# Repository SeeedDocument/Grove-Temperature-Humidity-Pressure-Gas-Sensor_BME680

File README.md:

# Grove-Temperature-Humidity-Pressure-Gas-Sensor_BME680

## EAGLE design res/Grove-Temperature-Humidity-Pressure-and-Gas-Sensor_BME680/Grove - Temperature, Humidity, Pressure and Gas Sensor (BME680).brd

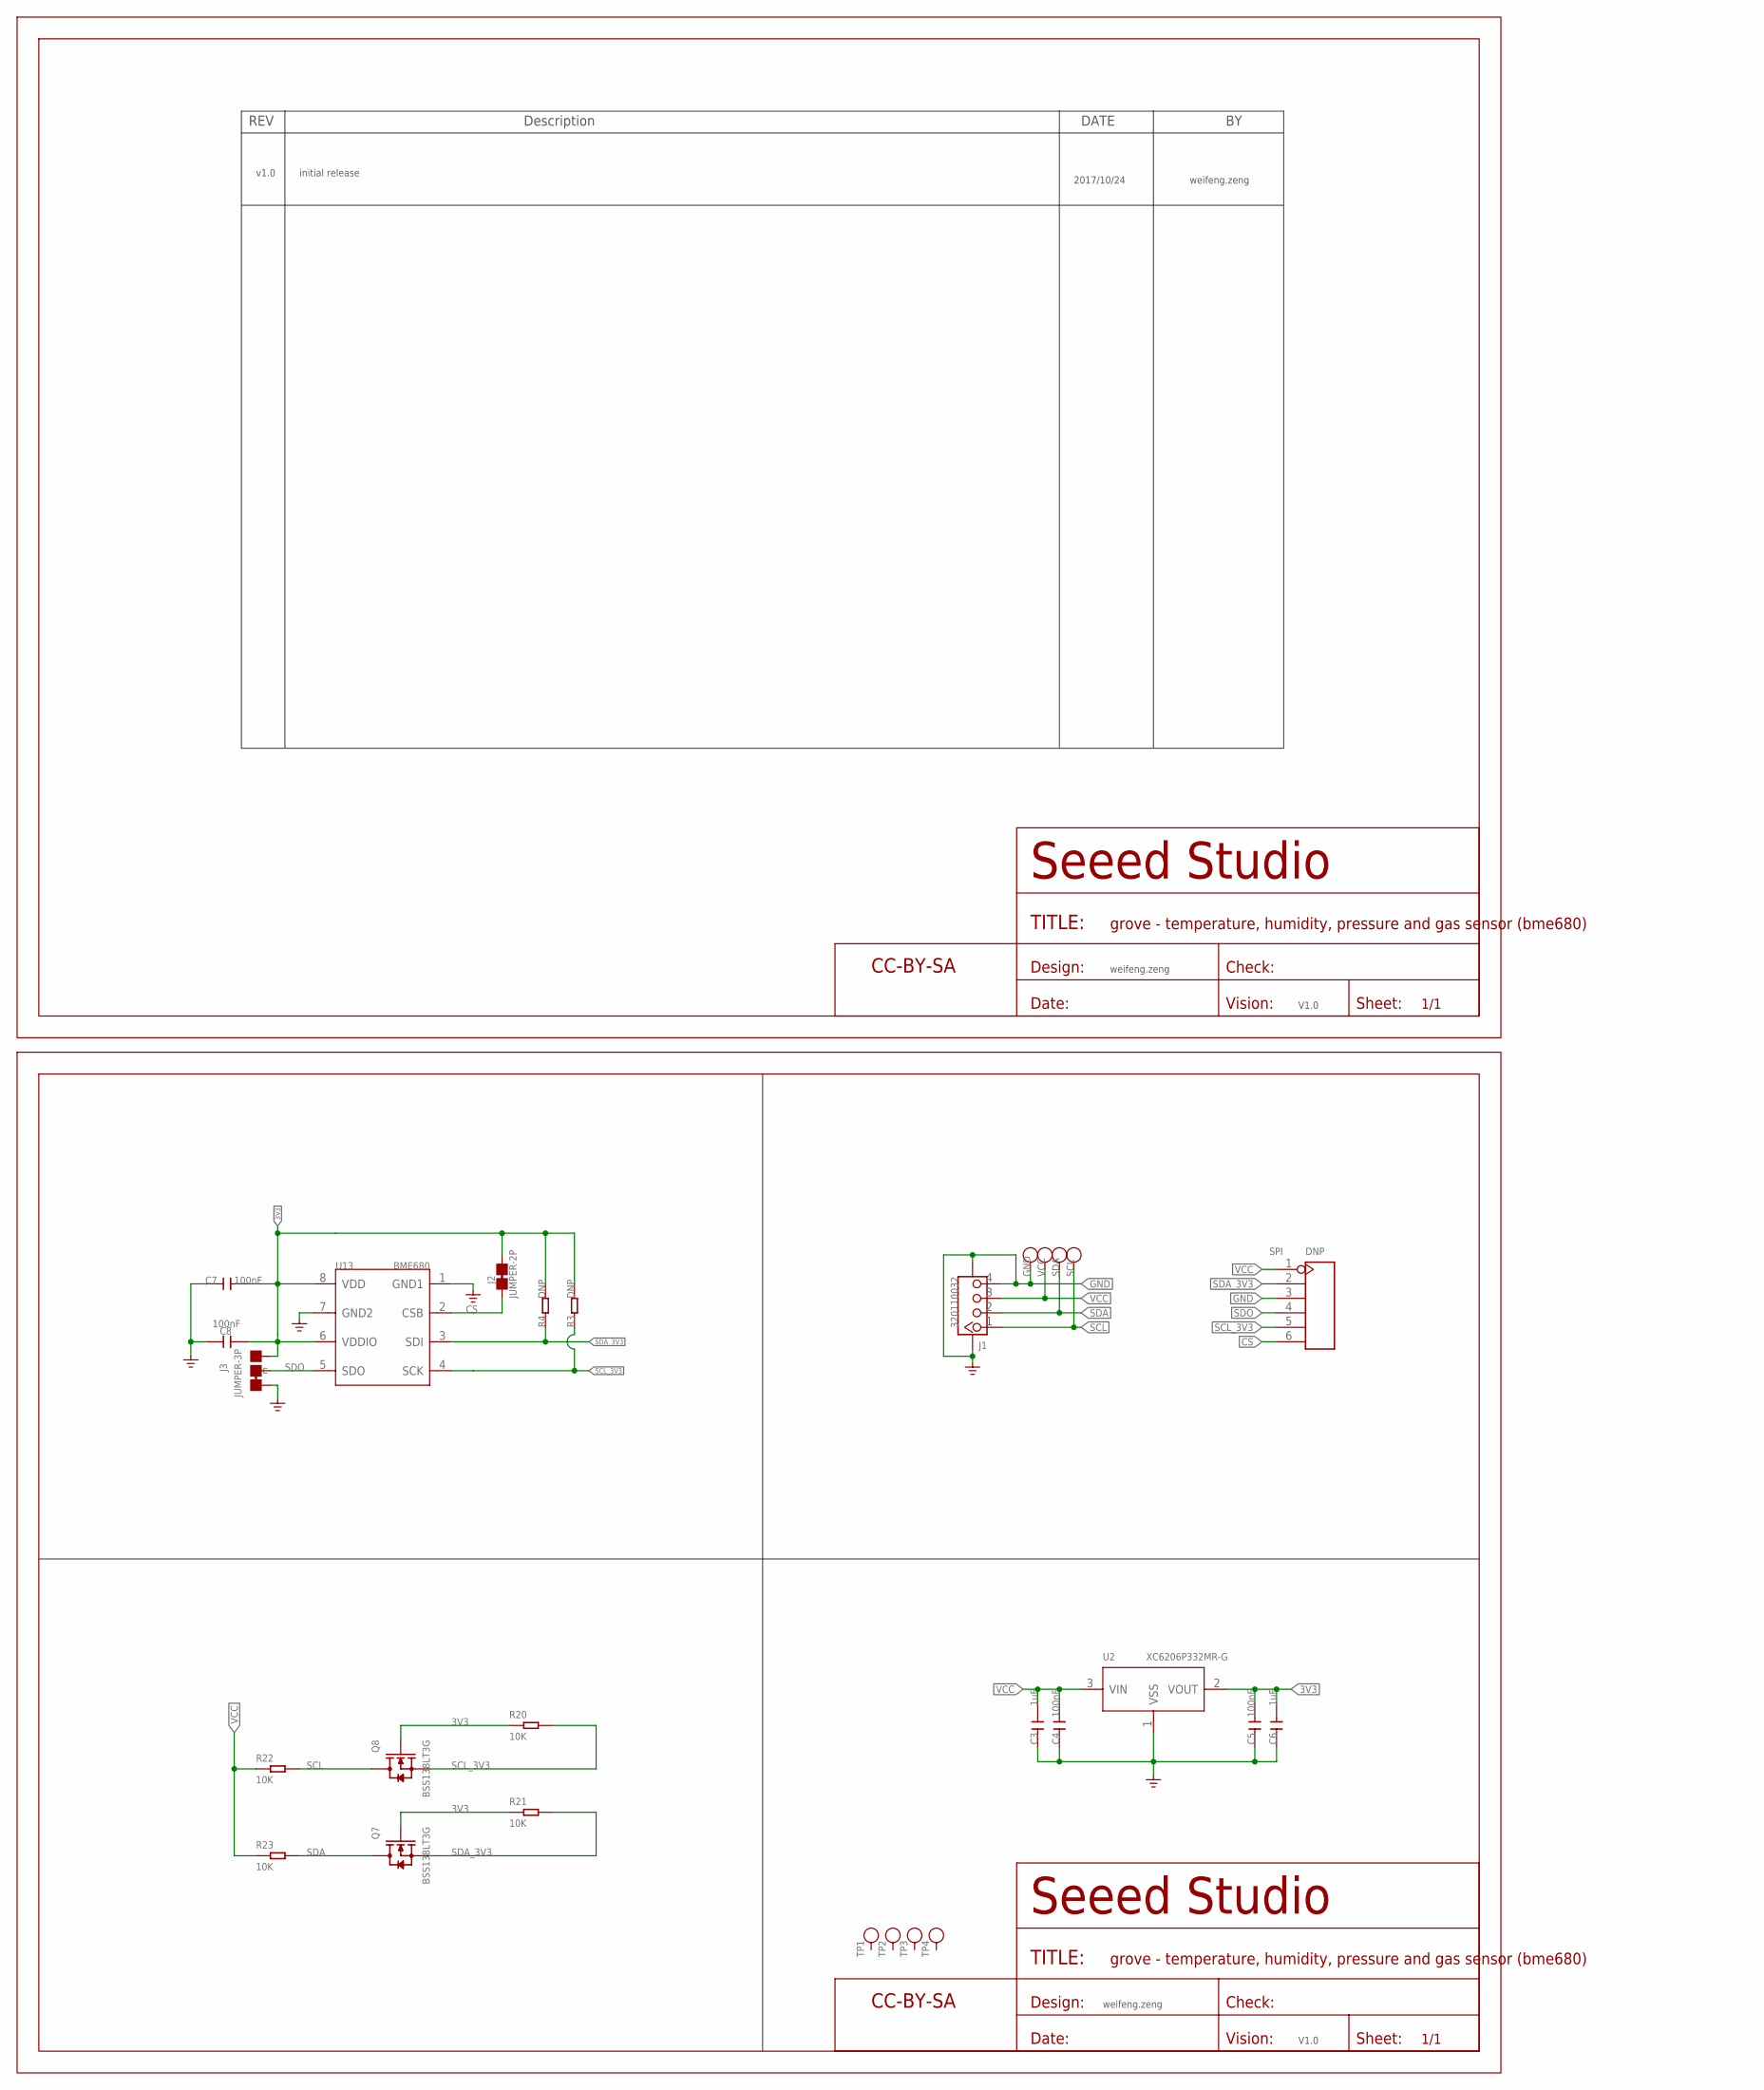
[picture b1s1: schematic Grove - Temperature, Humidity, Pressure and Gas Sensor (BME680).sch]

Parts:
C3, C6: 1uF; C0603
C4, C5, C7, C8: 100nF; C0603
FR1, FR2: SEEEDSTUDIO-OPEN-SCH-FRAME; SEEEDSTUDIO-PCB-FRAME
GND: TEST-POINT'4545'; TP-D45MIL
J1: 320110032; HW4-SMD-2.0-90D
J2: JUMPER-2P; 2P-SMD-SHORT
J3: JUMPER-3P; 3P-SMD-SHORT
Q7, Q8: BSS138LT3G; SOT-23
R3, R4: DNP; R0603
R20, R21, R22, R23: 10K; R0603
SCL: TEST-POINT'4545'; TP-D45MIL
SDA: TEST-POINT'4545'; TP-D45MIL
SPI: DNP; H6-2.54-C65D35MIL
TP1, TP2, TP3, TP4: TEST-POINT'4545'; TP-D45MIL
U2: XC6206P332MR-G; SOT-23
U13: BME680; SNR8-0.8-3X3X0.93MM
VCC: TEST-POINT'4545'; TP-D45MIL

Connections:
3V3: C5.1, C6.1, C7.2, C8.2, J2.2, J3.00 (R), Q7.1 (G), Q8.1 (G), R3.2, R4.2, R20.1, R21.1, U2.2 (VOUT), U13.6 (VDDIO), U13.8 (VDD)
CS: J2.1, SPI.6, U13.2 (CSB)
GND: C3.2, C4.2, C5.2, C6.2, C7.1, C8.1, GND.T, J1.4, J1.SS1, J1.SS2, J3.11 (L), SPI.3, U2.1 (VSS), U13.1 (GND1), U13.7 (GND2)
SCL: J1.1, Q8.3 (D), R22.2, SCL.T
SCL_3V3: Q8.2 (S), R3.1, R20.2, SPI.5, U13.4 (SCK)
SDA: J1.2, Q7.3 (D), R23.2, SDA.T
SDA_3V3: Q7.2 (S), R4.1, R21.2, SPI.2, U13.3 (SDI)
SDO: J3.MM (C), SPI.4, U13.5 (SDO)
VCC: C3.1, C4.1, J1.3, R22.1, R23.1, SPI.1, U2.3 (VIN), VCC.T

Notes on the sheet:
v1.0
initial release
2017/10/24
weifeng.zeng
V1.0

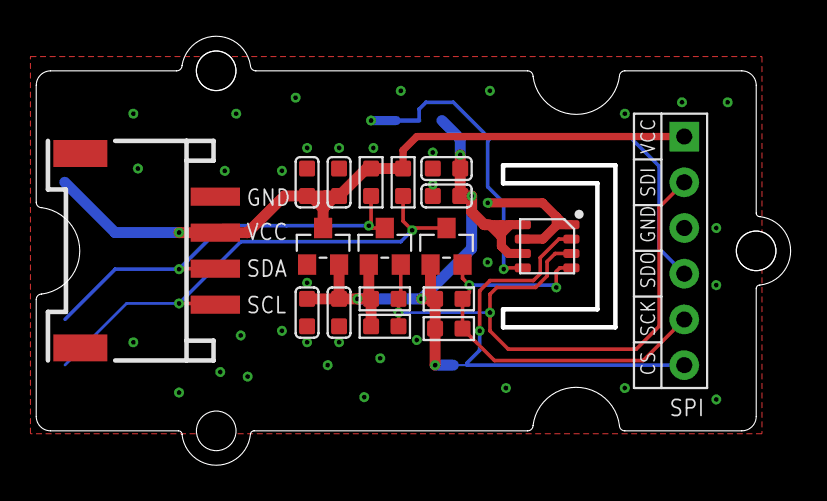
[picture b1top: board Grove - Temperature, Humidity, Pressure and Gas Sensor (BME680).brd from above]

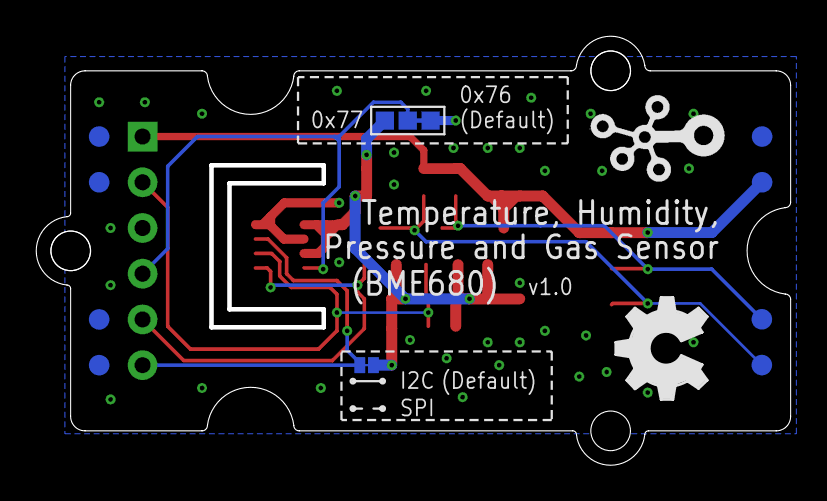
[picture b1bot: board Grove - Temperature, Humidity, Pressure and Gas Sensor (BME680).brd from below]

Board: 2 copper layers, 41.9 x 23.8 mm, 33 parts (12 on the bottom side), 9 nets.

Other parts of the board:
U10: GROVE-TEST-PLATFORM
U$3: OSHW_FILLX200_NOTEXT
U$4: TWIGLOGO

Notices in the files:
parts and their libraries:
moudle-new: This work is licensed under the Creative Commons Attribution 4.0 International License.
To view a copy of this license,visit:
http://creativecommons.org/licenses/by-sa/4.0
moudle-new: CC-BY-SA
